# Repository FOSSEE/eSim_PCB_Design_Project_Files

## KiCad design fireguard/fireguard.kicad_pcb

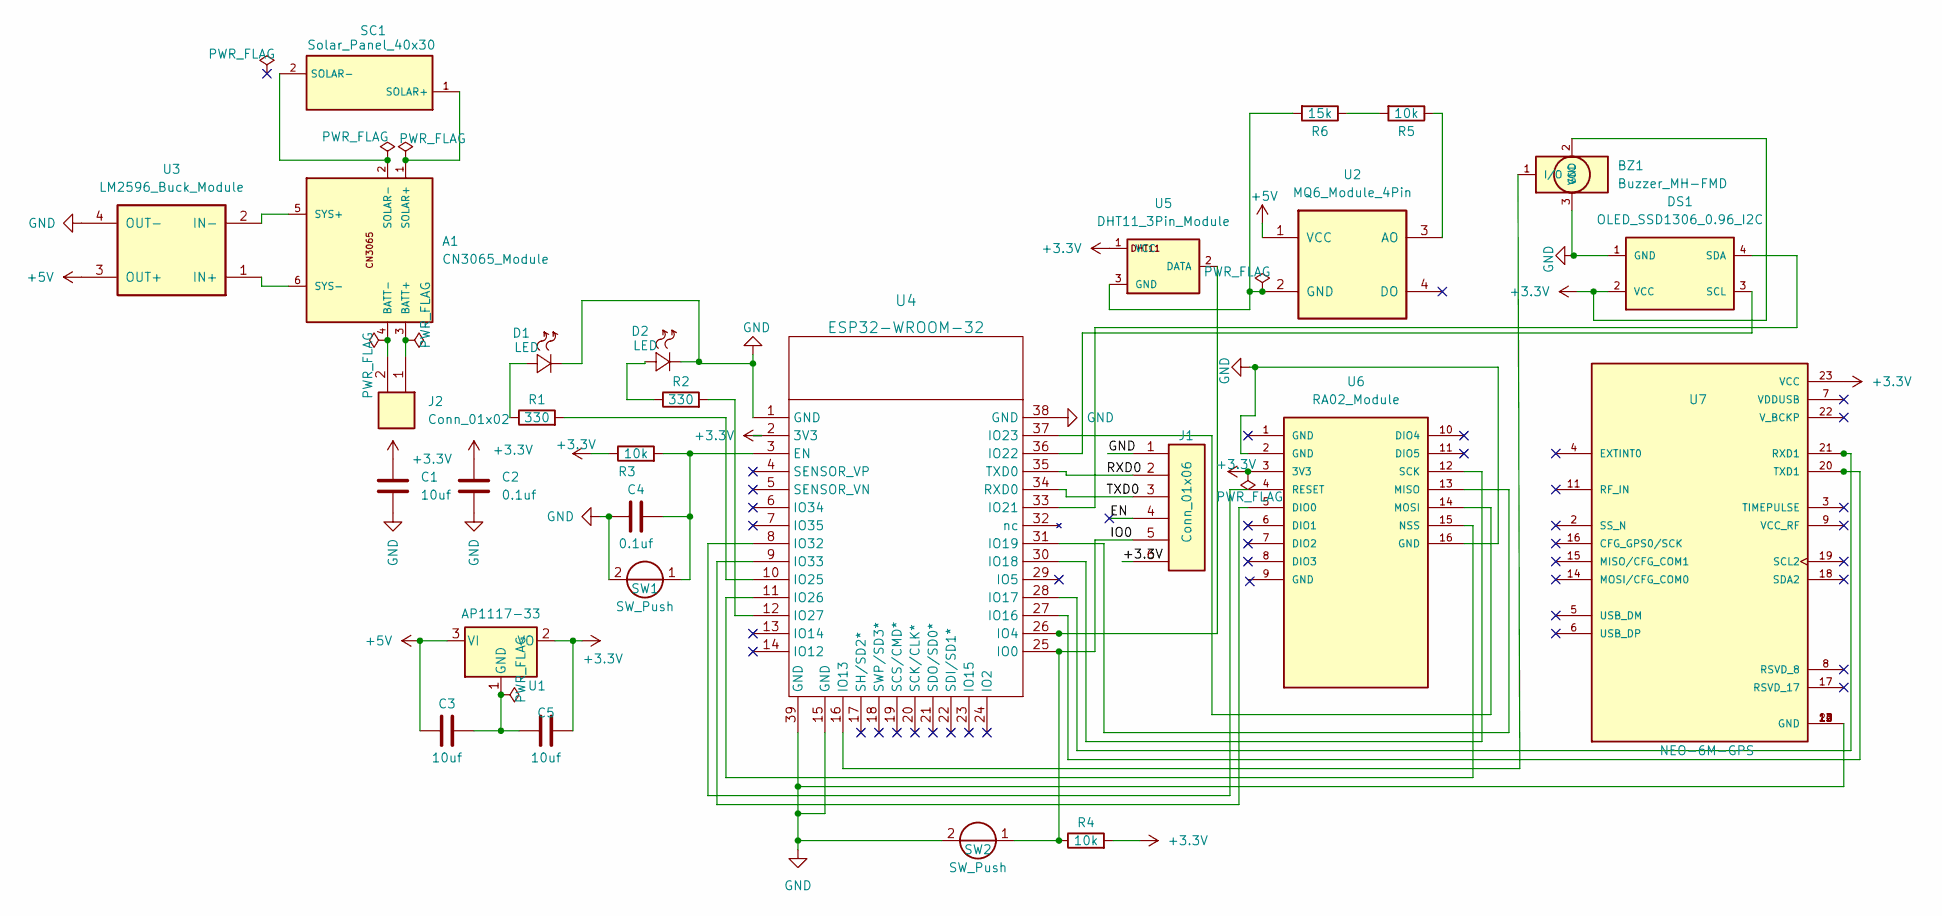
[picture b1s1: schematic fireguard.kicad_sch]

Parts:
A1: CN3065_Module; PinHeader_1x06_P2.54mm_Vertical
BZ1: Buzzer_MH-FMD; PinHeader_1x03_P2.54mm_Vertical_SMD_Pin1Right
C1, C3, C5: 10uf; CP_Radial_D5.0mm_P2.00mm
C2, C4: 0.1uf; C_Disc_D5.0mm_W2.5mm_P5.00mm
D1, D2: LED; LED_D5.0mm
DS1: OLED_SSD1306_0.96_I2C; PinHeader_1x04_P2.54mm_Vertical
J1: Conn_01x06; PinHeader_1x06_P2.54mm_Vertical
J2: Conn_01x02; PinHeader_1x02_P2.54mm_Vertical
R1, R2: 330; R_Axial_DIN0207_L6.3mm_D2.5mm_P10.16mm_Horizontal
R3, R4, R5: 10k; R_Axial_DIN0207_L6.3mm_D2.5mm_P10.16mm_Horizontal
R6: 15k; R_Axial_DIN0207_L6.3mm_D2.5mm_P10.16mm_Horizontal
SC1: Solar_Panel_40x30; PinHeader_1x02_P2.54mm_Vertical
SW1, SW2: SW_Push; SW_PUSH_6mm
U1: AP1117-33; SOT-223-3_TabPin2
U2: MQ6_Module_4Pin; PinHeader_1x04_P2.54mm_Vertical
U3: LM2596_Buck_Module; PinHeader_1x04_P2.54mm_Vertical
U4: ESP32-WROOM-32
U5: DHT11_3Pin_Module; PinHeader_1x03_P2.54mm_Vertical_SMD_Pin1Left
U6: RA02_Module; PinHeader_1x16_P2.54mm_Vertical_SMD_Pin1Right
U7: NEO-6M-GPS; ublox_NEO; PARTREV R15

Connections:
+3.3V: BZ1.2 (VCC), C1.1, C2.1, C5.2, DS1.2 (VCC), J1.6, R3.1, R4.2, U1.2 (VO), U4.2 (3V3), U5.1 (VCC), U6.3 (3V3), U7.23 (VCC)
+5V: C3.1, U1.3 (VI), U2.1 (VCC), U3.3 (OUT+)
/EN: J1.4
/IO0: J1.5, R4.1, SW2.1, U4.25 (IO0)
/RXD0: J1.2, U4.35 (TXD0)
/TXD0: J1.3, U4.34 (RXD0)
GND: BZ1.3 (GND), C1.2, C2.2, C4.2, D1.2 (-), D2.2 (-), DS1.1 (GND), J1.1, SW1.2, SW2.2, U3.4 (OUT-), U4.1 (GND), U4.15 (GND), U4.38 (GND), U4.39 (GND), U6.2 (GND), U6.16 (GND), U7.10 (GND), U7.12 (GND), U7.13 (GND), U7.24 (GND)
unnamed: A1.1 (SOLAR+), SC1.1 (SOLAR+)
unnamed: A1.2 (SOLAR-), SC1.2 (SOLAR-)
unnamed: A1.3 (BATT+), J2.1
unnamed: A1.4 (BATT-), J2.2
unnamed: A1.5 (SYS+), U3.2 (IN-)
unnamed: A1.6 (SYS-), U3.1 (IN+)
unnamed: BZ1.1 (I/O), U4.16 (IO13)
unnamed: C3.2, C5.1, U1.1 (GND)
unnamed: C4.1, R3.2, SW1.1, U4.3 (EN)
unnamed: DS1.3 (SCL), U4.36 (IO22)
unnamed: DS1.4 (SDA), U4.33 (IO21)
unnamed: D1.1 (+), R1.1
unnamed: R1.2, U4.10 (IO25)
unnamed: D2.1 (+), R2.1
unnamed: R2.2, U4.12 (IO27)
unnamed: R5.1, U2.3 (AO)
unnamed: R5.2, R6.1
unnamed: R6.2, U2.2 (GND), U5.3 (GND)
unnamed: U4.8 (IO32), U6.4 (RESET)
unnamed: U4.9 (IO33), U6.5 (DIO0)
unnamed: U4.11 (IO26), U6.15 (NSS)
unnamed: U4.26 (IO4), U5.2 (DATA)
unnamed: U4.27 (IO16), U7.20 (TXD1)
unnamed: U4.28 (IO17), U7.21 (RXD1)
unnamed: U4.30 (IO18), U6.12 (SCK)
unnamed: U4.31 (IO19), U6.13 (MISO)
unnamed: U4.37 (IO23), U6.14 (MOSI)

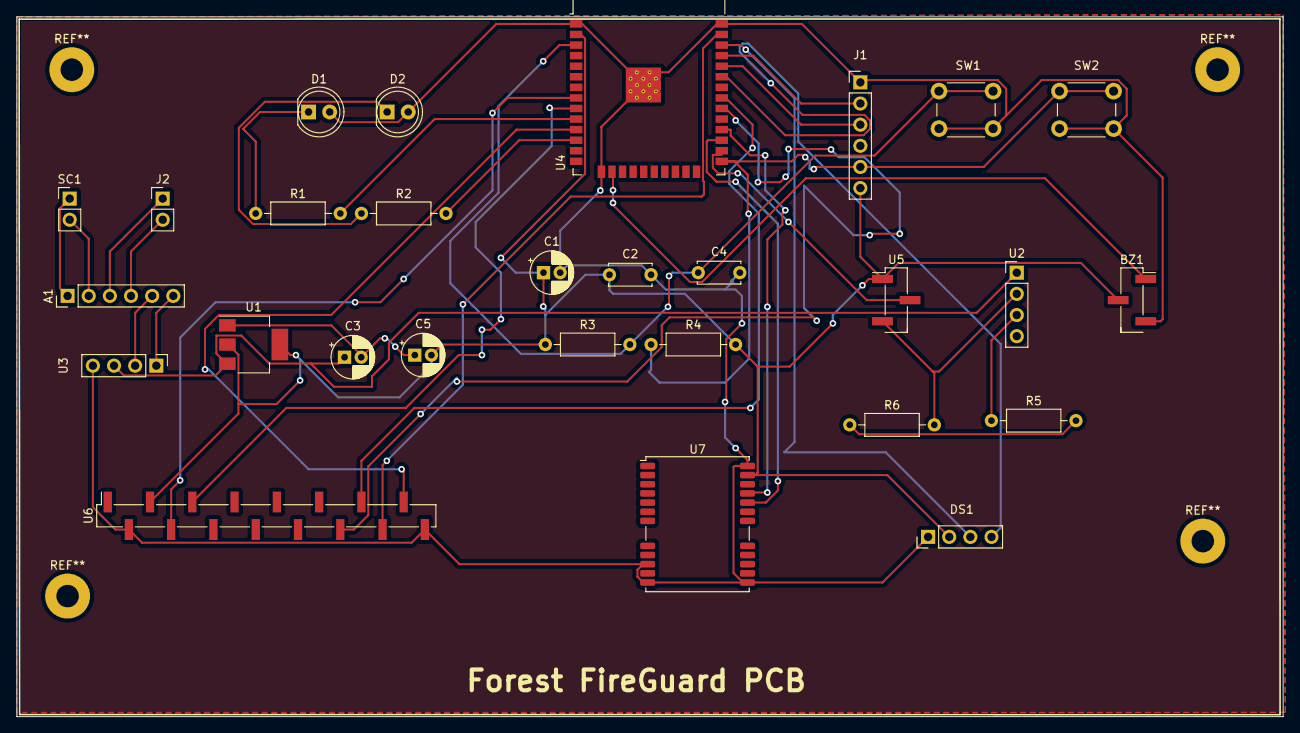
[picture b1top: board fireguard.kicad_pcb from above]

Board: 2 copper layers, 152.1 x 84.1 mm, 28 parts (0 on the bottom side), 33 nets.

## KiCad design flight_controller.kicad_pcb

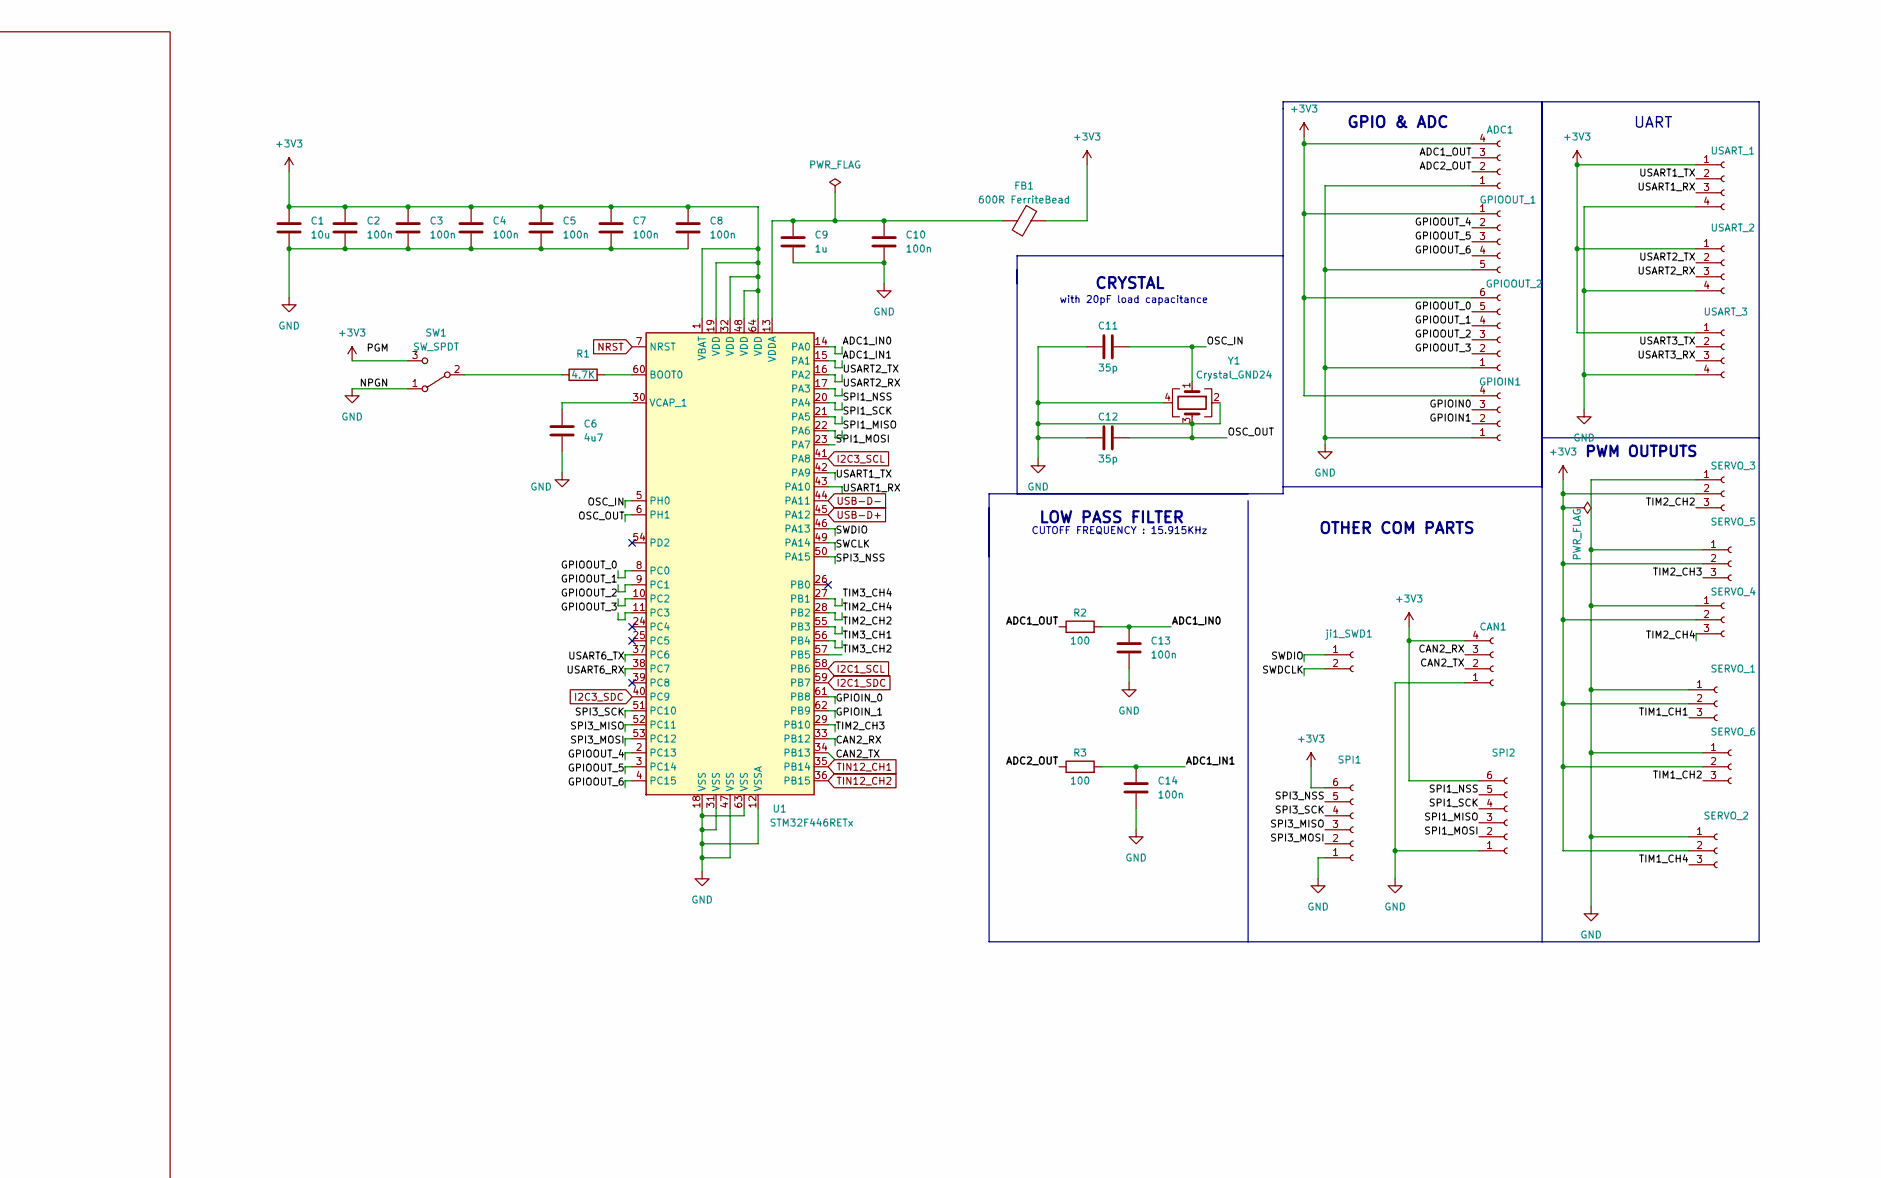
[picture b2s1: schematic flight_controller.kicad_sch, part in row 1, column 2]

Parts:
ADC1: PinHeader_1x04_P1.00mm_Vertical
C1: 10u; C_0603_1608Metric
C2, C3, C4, C5, C7, C8, C10, C13, C14: 100n; C_0603_1608Metric
C6: 4u7; C_0603_1608Metric
C9: 1u; C_0603_1608Metric
C11, C12: 35p; C_0603_1608Metric
CAN1: PinHeader_1x04_P1.00mm_Vertical
FB1: 600R FerriteBead; LairdTech_28C0236-0JW-10
GPIOIN1: PinHeader_1x04_P1.00mm_Vertical
GPIOOUT_1: PinHeader_1x05_P1.00mm_Vertical
GPIOOUT_2: PinHeader_1x06_P1.00mm_Vertical
R1: 4.7K; R_0603_1608Metric
R2, R3: 100; R_0603_1608Metric
SERVO_1, SERVO_2, SERVO_3, SERVO_4, SERVO_5, SERVO_6: PinHeader_1x03_P1.00mm_Vertical
SPI1, SPI2: PinHeader_1x06_P1.00mm_Vertical
SW1: SW_SPDT; SW_SPDT_CK-JS102011SAQN
U1: STM32F446RETx; LQFP-64_10x10mm_P0.5mm
USART_1, USART_2, USART_3: PinHeader_1x04_P1.00mm_Vertical
Y1: Crystal_GND24; Crystal_SMD_0603-4Pin_6.0x3.5mm
ji1_SWD1: PinHeader_1x02_P1.00mm_Vertical

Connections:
+3V3: ADC1.4, C1.1, C2.1, C3.1, C4.1, C5.1, C7.1, C8.1, CAN1.4, FB1.1, GPIOIN1.4, GPIOOUT_1.1, GPIOOUT_2.6, SERVO_1.2, SERVO_2.2, SERVO_3.2, SERVO_4.2, SERVO_5.2, SERVO_6.2, SPI1.6, SPI2.6, SW1.3 (C), U1.1 (VBAT), U1.19 (VDD), U1.32 (VDD), U1.48 (VDD), U1.64 (VDD), USART_1.1, USART_2.1, USART_3.1; also elsewhere on the board
/ADC1_IN0: C13.1, R2.2, U1.14 (PA0)
/ADC1_IN1: C14.1, R3.2, U1.15 (PA1)
/ADC1_OUT: ADC1.3, R2.1
/ADC2_OUT: ADC1.2, R3.1
/CAN2_RX: CAN1.3, U1.33 (PB12)
/CAN2_TX: CAN1.2, U1.34 (PB13)
/GPIOIN0: GPIOIN1.3
/GPIOIN1: GPIOIN1.2
/GPIOIN_0: U1.61 (PB8)
/GPIOIN_1: U1.62 (PB9)
/GPIOOUT_0: GPIOOUT_2.5, U1.8 (PC0)
/GPIOOUT_1: GPIOOUT_2.4, U1.9 (PC1)
/GPIOOUT_2: GPIOOUT_2.3, U1.10 (PC2)
/GPIOOUT_3: GPIOOUT_2.2, U1.11 (PC3)
/GPIOOUT_4: GPIOOUT_1.2, U1.2 (PC13)
/GPIOOUT_5: GPIOOUT_1.3, U1.3 (PC14)
/GPIOOUT_6: GPIOOUT_1.4, U1.4 (PC15)
/OSC_IN: C11.2, U1.5 (PH0), Y1.1
/SPI1_MISO: SPI2.3, U1.22 (PA6)
/SPI1_MOSI: SPI2.2, U1.23 (PA7)
/SPI1_NSS: SPI2.5, U1.20 (PA4)
/SPI1_SCK: SPI2.4, U1.21 (PA5)
/SPI3_MISO: SPI1.3, U1.52 (PC11)
/SPI3_MOSI: SPI1.2, U1.53 (PC12)
/SPI3_NSS: SPI1.5, U1.50 (PA15)
/SPI3_SCK: SPI1.4, U1.51 (PC10)
/SWCLK: U1.49 (PA14)
/SWDCLK: ji1_SWD1.2
/SWDIO: U1.46 (PA13), ji1_SWD1.1
/TIM1_CH1: SERVO_1.3
/TIM1_CH2: SERVO_6.3
/TIM1_CH4: SERVO_2.3
/TIM2_CH2: SERVO_3.3, U1.55 (PB3)
/TIM2_CH3: SERVO_5.3, U1.29 (PB10)
/TIM2_CH4: SERVO_4.3, U1.28 (PB2)
/TIM3_CH1: U1.56 (PB4)
/TIM3_CH2: U1.57 (PB5)
/TIM3_CH4: U1.27 (PB1)
/USART1_RX: U1.43 (PA10), USART_1.3
/USART1_TX: U1.42 (PA9), USART_1.2
/USART2_RX: U1.17 (PA3), USART_2.3
/USART2_TX: U1.16 (PA2), USART_2.2
/USART3_RX: USART_3.3
/USART3_TX: USART_3.2
/USART6_RX: U1.38 (PC7)
/USART6_TX: U1.37 (PC6)
GND: ADC1.1, C1.2, C2.2, C3.2, C4.2, C5.2, C6.2, C7.2, C8.2, C9.2, C10.2, C11.1, C12.1, C12.2, C13.2, C14.2, CAN1.1, GPIOIN1.1, GPIOOUT_1.5, GPIOOUT_2.1, SERVO_1.1, SERVO_2.1, SERVO_3.1, SERVO_4.1, SERVO_5.1, SERVO_6.1, SPI1.1, SPI2.1, SW1.1 (A), U1.6 (PH1), U1.12 (VSSA), U1.18 (VSS), U1.31 (VSS), U1.47 (VSS), U1.63 (VSS), USART_1.4, USART_2.4, USART_3.4, Y1.2, Y1.3, Y1.4; also elsewhere on the board
I2C1_SCL: U1.58 (PB6); also elsewhere on the board
I2C1_SDC: U1.59 (PB7)
I2C3_SCL: U1.41 (PA8); also elsewhere on the board
I2C3_SDC: U1.40 (PC9)
NRST: U1.7 (NRST); also elsewhere on the board
unnamed: C6.1, U1.30 (VCAP_1)
unnamed: C9.1, C10.1, FB1.2, U1.13 (VDDA)
unnamed: R1.1, SW1.2 (B)
unnamed: R1.2, U1.60 (BOOT0)
TIN12_CH1: U1.35 (PB14)
TIN12_CH2: U1.36 (PB15)
USB-D+: U1.45 (PA12)
USB-D-: U1.44 (PA11); also elsewhere on the board

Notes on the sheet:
CUTOFF FREQUENCY : 15.915KHz
UART
GPIO & ADC
CRYSTAL
PWM OUTPUTS
with 20pF load capacitance
LOW PASS FILTER
OTHER COM PARTS

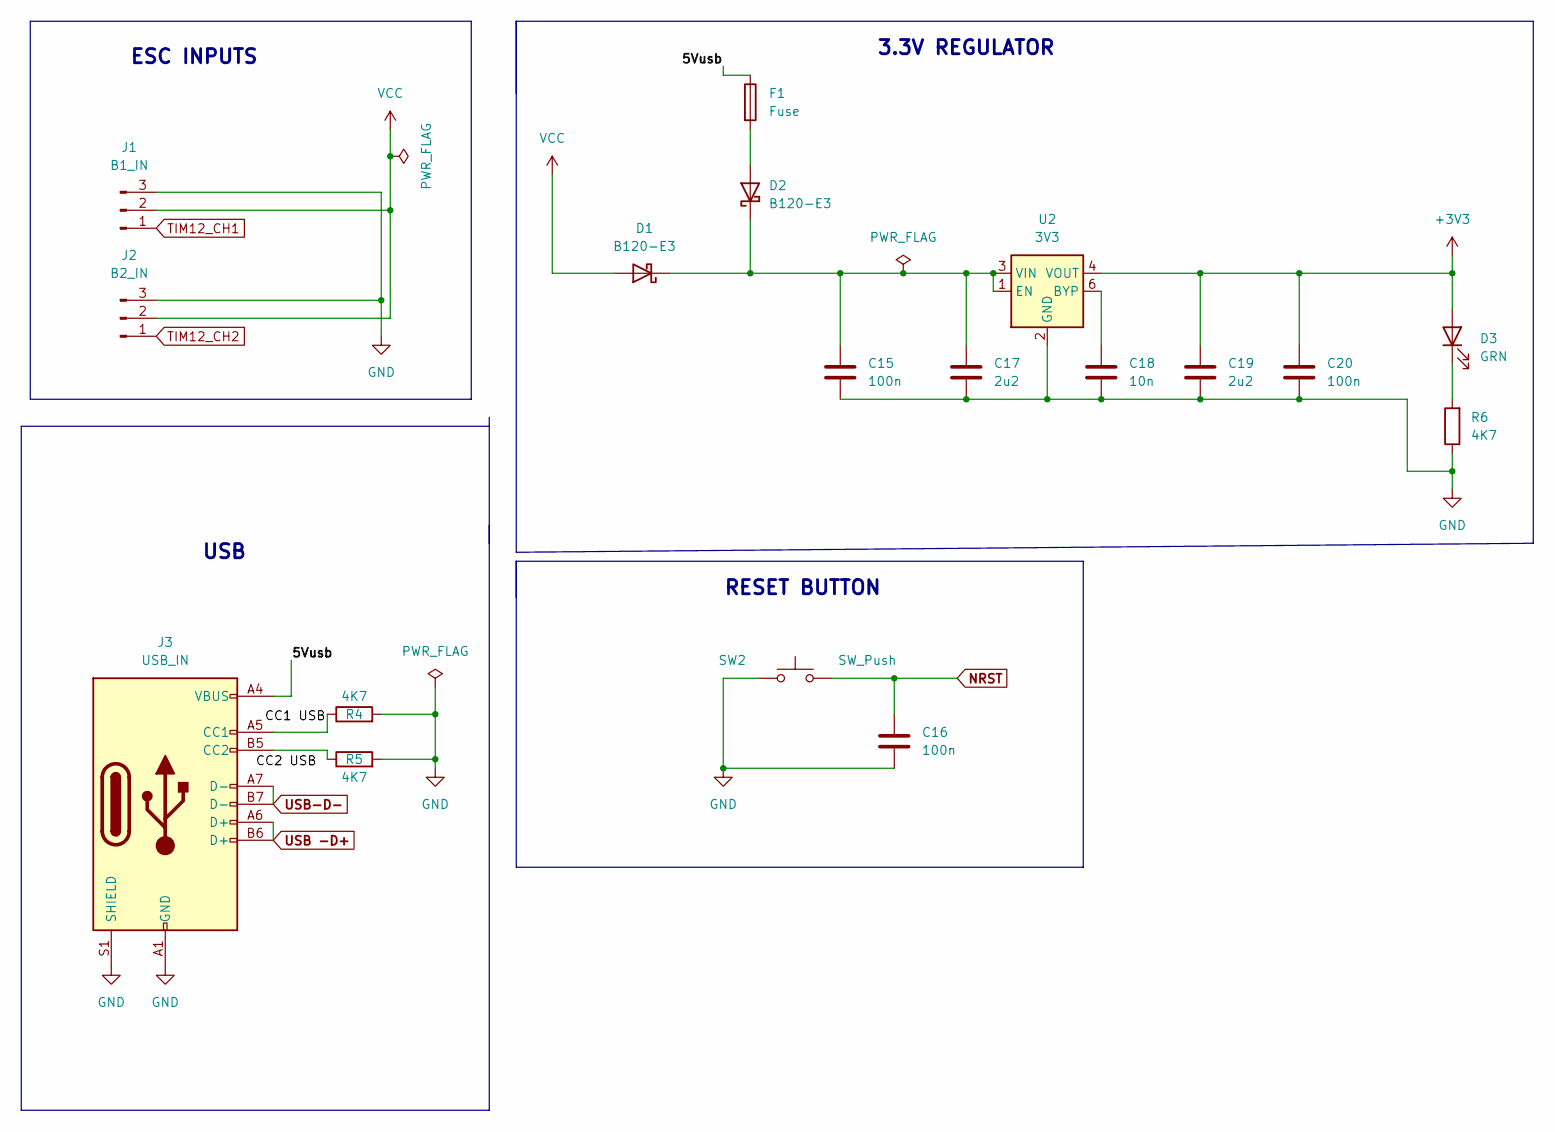
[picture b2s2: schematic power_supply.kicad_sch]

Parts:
C15, C16, C20: 100n; C_0603_1608Metric
C17, C19: 2u2; C_0603_1608Metric
C18: 10n; C_0603_1608Metric
D1, D2: B120-E3; D_SMA
D3: GRN; LED_0603_1608Metric
F1: Fuse; Fuse_0603_1608Metric
J1: B1_IN; FanPinHeader_1x03_P2.54mm_Vertical
J2: B2_IN; FanPinHeader_1x03_P2.54mm_Vertical
J3: USB_IN; USB_C_Receptacle_Amphenol_12401610E4-2A
R4, R5, R6: 4K7; R_0603_1608Metric
SW2: SW_Push; SW_PUSH-12mm
U2: 3V3; MLF-6-1EP_1.6x1.6mm_P0.5mm_EP0.5x1.26mm

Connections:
+3V3: C19.1, C20.1, D3.2 (A), U2.4 (VOUT); also elsewhere on the board
/POWER/5Vusb: F1.1, J3.A4 (VBUS), J3.A9 (VBUS), J3.B4 (VBUS), J3.B9 (VBUS)
GND: C15.2, C16.2, C17.2, C18.2, C19.2, C20.2, J1.3, J2.3, J3.A1 (GND), J3.A12 (GND), J3.B1 (GND), J3.B12 (GND), J3.S1 (SHIELD), R4.2, R5.2, R6.1, SW2.1, U2.2 (GND), U2.7 (GND); also elsewhere on the board
NRST: C16.1, SW2.2; also elsewhere on the board
unnamed: C15.1, C17.1, D1.1 (K), D2.1 (K), U2.1 (EN), U2.3 (VIN)
unnamed: C18.1, U2.6 (BYP)
unnamed: D2.2 (A), F1.2
unnamed: D3.1 (K), R6.2
unnamed: J3.A5 (CC1), R4.1
unnamed: J3.B5 (CC2), R5.1
TIM12_CH1: J1.1
TIM12_CH2: J2.1
USB -D+: J3.A6 (D+), J3.B6 (D+)
USB-D-: J3.A7 (D-), J3.B7 (D-); also elsewhere on the board
VCC: D1.2 (A), J1.2, J2.2

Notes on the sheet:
RESET BUTTON
USB
3.3V REGULATOR
ESC INPUTS

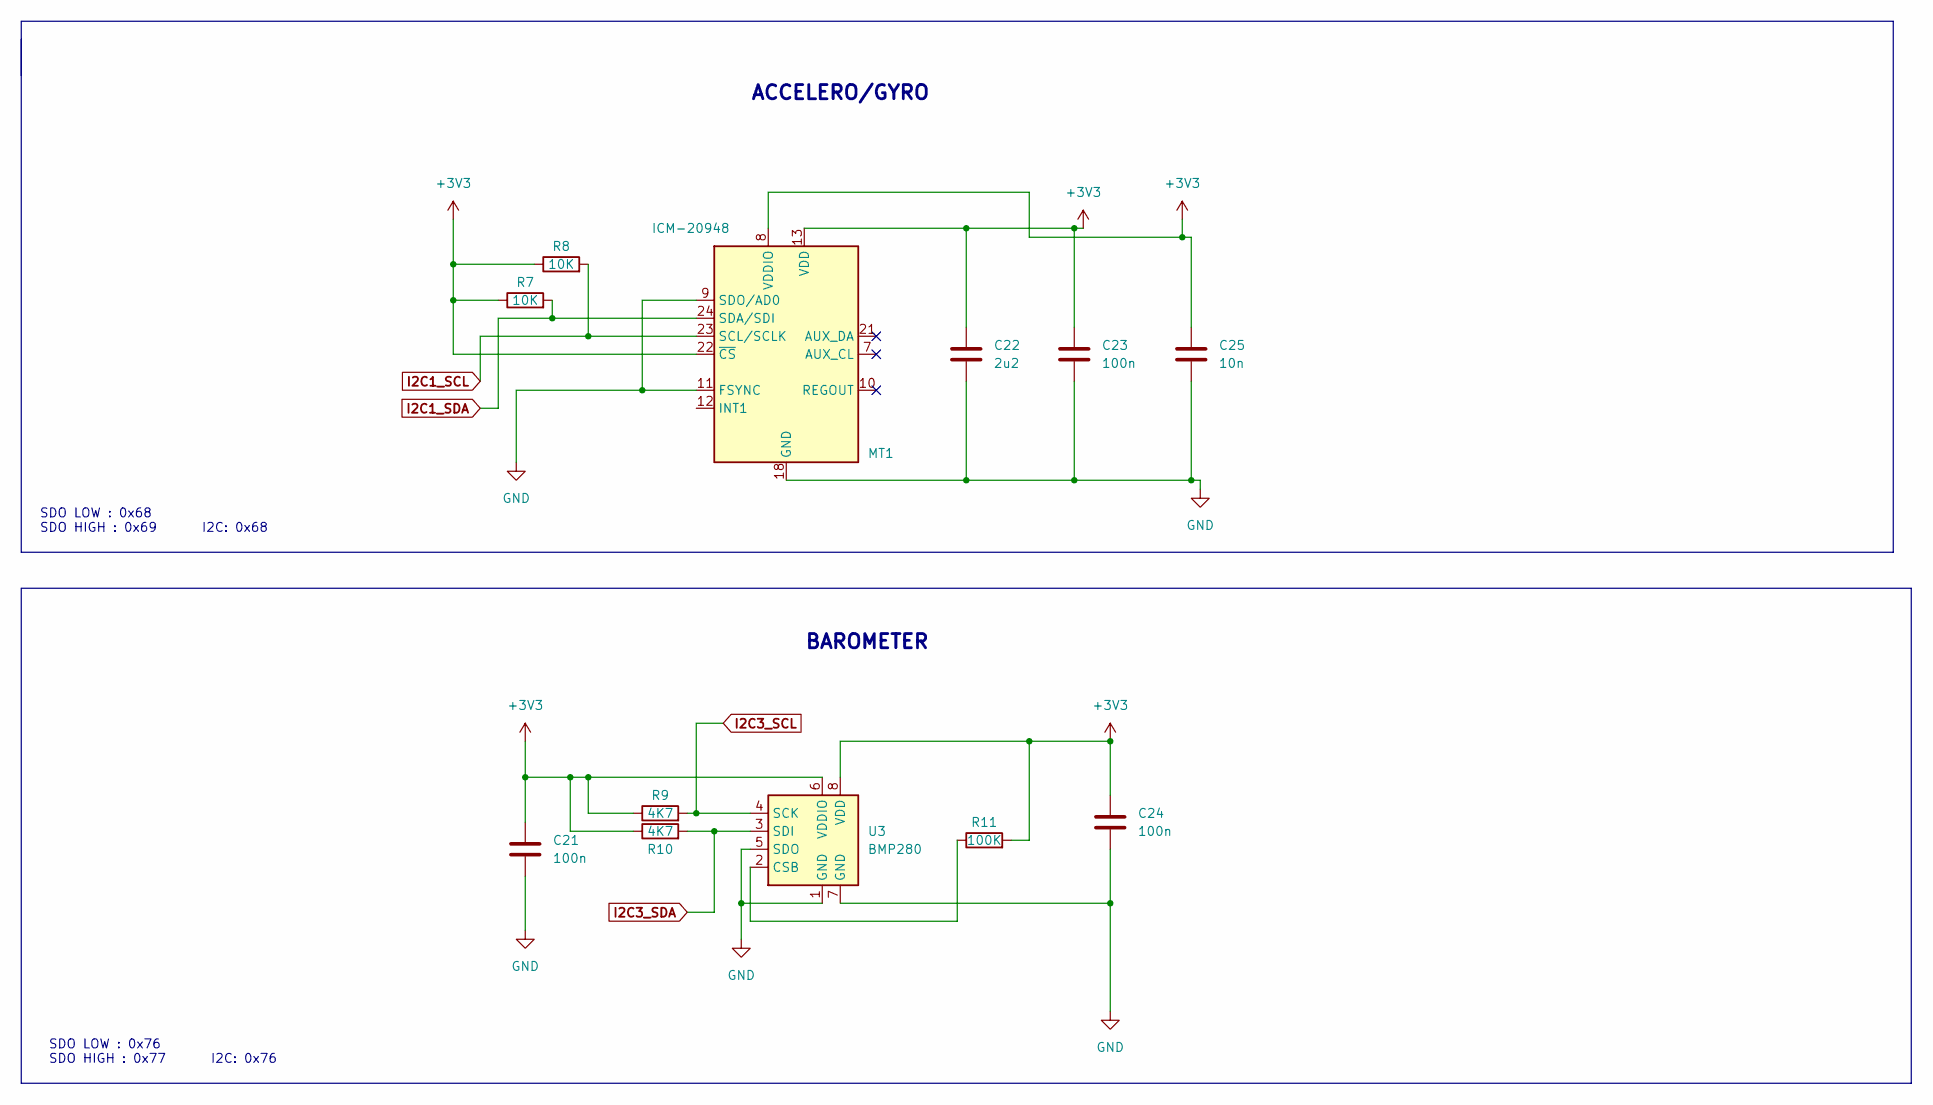
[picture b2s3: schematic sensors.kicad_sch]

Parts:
C21, C23, C24: 100n; C_0603_1608Metric
C22: 2u2; C_0603_1608Metric
C25: 10n; C_0603_1608Metric
MT1: ICM-20948; InvenSense_QFN-24_3x3mm_P0.4mm
R7, R8: 10K; R_0603_1608Metric
R9, R10: 4K7; R_0603_1608Metric
R11: 100K; R_0603_1608Metric
U3: BMP280; Bosch_LGA-8_2x2.5mm_P0.65mm_ClockwisePinNumbering

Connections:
+3V3: C21.1, C22.1, C23.1, C24.1, C25.1, MT1.8 (VDDIO), MT1.13 (VDD), MT1.22 (~CS), R7.1, R8.1, R9.1, R10.1, R11.2, U3.6 (VDDIO), U3.8 (VDD); also elsewhere on the board
GND: C21.2, C22.2, C23.2, C24.2, C25.2, MT1.9 (SDO/AD0), MT1.11 (FSYNC), MT1.18 (GND), MT1.20 (GND), U3.1 (GND), U3.5 (SDO), U3.7 (GND); also elsewhere on the board
I2C1_SCL: MT1.23 (SCL/SCLK), R8.2; also elsewhere on the board
I2C1_SDA: MT1.24 (SDA/SDI), R7.2
I2C3_SCL: R9.2, U3.4 (SCK); also elsewhere on the board
I2C3_SDA: R10.2, U3.3 (SDI)
unnamed: R11.1, U3.2 (CSB)

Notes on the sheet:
BAROMETER
ACCELERO/GYRO
I2C: 0x68
SDO LOW : 0x76 SDO HIGH : 0x77
SDO LOW : 0x68 SDO HIGH : 0x69
I2C: 0x76

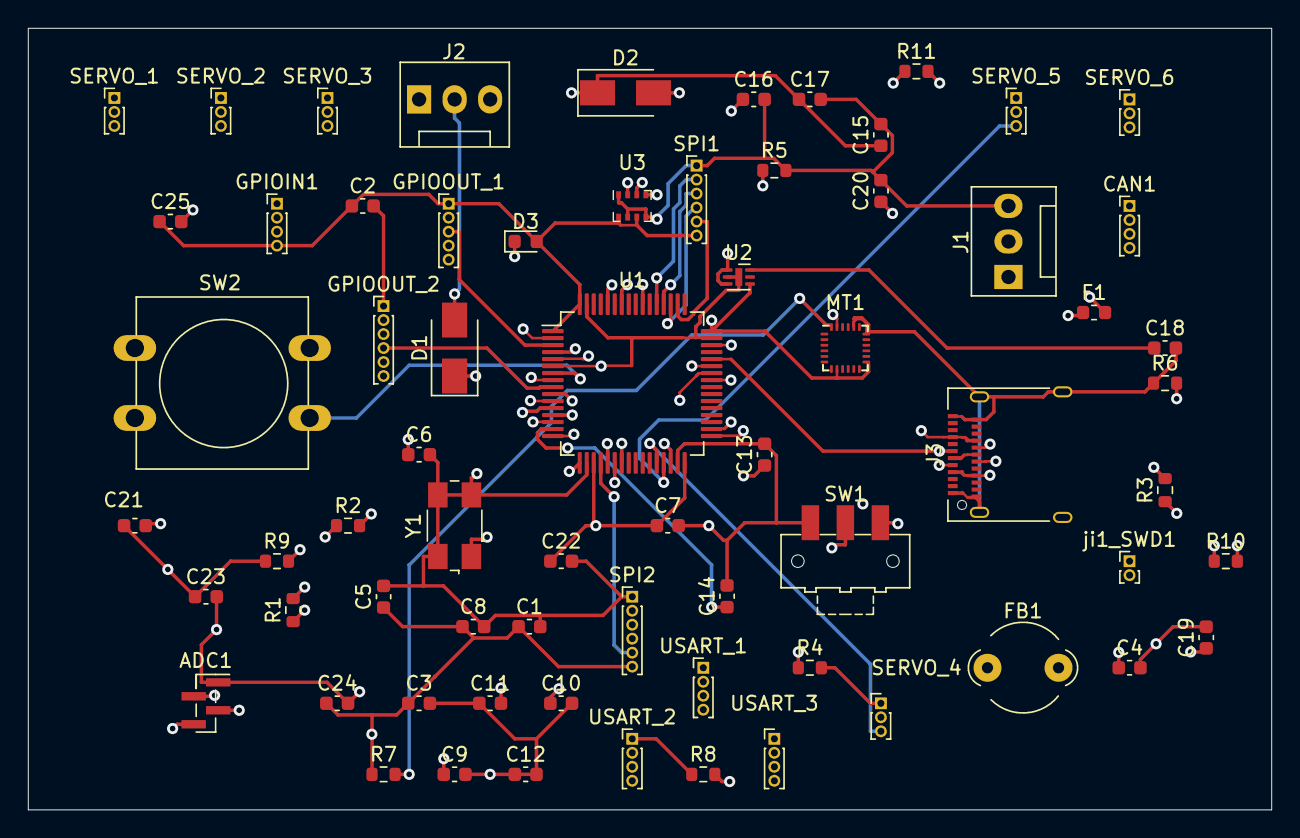
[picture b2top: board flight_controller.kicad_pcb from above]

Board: 4 copper layers, 88.9 x 55.9 mm, 68 parts (0 on the bottom side), 52 nets.

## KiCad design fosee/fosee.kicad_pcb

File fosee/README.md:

# ATmega328P Environment Monitor (eSim 2.5 PCB Project)

A 2-layer PCB design for a small environment-monitoring board built around an **ATmega328P (ATMEGA328P-AU, TQFP-32)**. The board reads temperature/humidity (DHT11) and ambient light (LDR), shows data on an I2C OLED, gives feedback through three status LEDs and a buzzer, and can be programmed over ICSP or a UART header.

- **Author:** Mohnish Sathiamurthy, Dept. of ECE, Chennai Institute of Technology
- **Tool:** eSim 2.5 (Eeschema / Pcbnew, KiCad 6.0 file format)
- **Board:** 2 layers, [100 x 80] mm, GND copper pour on the bottom layer
- **Status:** schematic complete, layout complete, DRC: [fill in result, e.g. 0 errors / 0 unconnected]

> Items in `[square brackets]` are values to confirm or fill in from your final design before submission.

---

## 1. Features

| Function | Implementation |
|---|---|
| Processing | ATmega328P-AU, 16 MHz crystal, 5 V |
| Power input | DC barrel jack, reverse-polarity diode, L7805 (5 V), AMS1117-3.3 (3.3 V) |
| Programming | 6-pin ICSP header, 4-pin UART header |
| Sensing | DHT11 (temperature/humidity) header, LDR light divider on ADC0 |
| Display | 4-pin I2C OLED header (3.3 V, with 4.7 kOhm pull-ups) |
| Indicators | 3 status LEDs (330 Ohm), buzzer driven by BC547 with flyback diode |
| Mechanical | 4 x M3 mounting holes, connectors placed on the board edges |

## 2. Circuit description

**Power.** The jack (J1) feeds D1 (1N4007, reverse-polarity protection) to the `VIN` rail. U1 (L7805) generates the 5 V `VCC` rail (C1 0.33 uF in, C2 0.1 uF out). U2 (AMS1117-3.3) takes `VCC` and generates `+3V3` for the OLED (C3 10 uF in, C4 22 uF out).

**Microcontroller.** U3 is powered from `VCC` on VCC and AVCC pins, each decoupled with 100 nF (C5, C6, C7). AREF is decoupled with C8 (100 nF). All GND pins connect to the ground plane.

**Clock and reset.** Y1 (16 MHz) with C9/C10 (22 pF) sits on XTAL1/XTAL2. RESET is pulled up by R1 (10 kOhm) with SW1 to ground, and is also brought to the ICSP header.

**Sensors.** The DHT11 data line (PD2) has a 10 kOhm pull-up (R2). The LDR (J6) forms a divider with R3 (10 kOhm); the midpoint `LDR_OUT` goes to PC0 (ADC0).

**Display.** The OLED header (J5) uses PC4 (SDA) and PC5 (SCL) with 4.7 kOhm pull-ups (R4, R5) to 3.3 V.

**Outputs.** PD4/PD5/PD6 drive LEDs D2-D4 through 330 Ohm resistors (R6-R8). PD7 drives Q1 (BC547) through R9 (1 kOhm); BZ1 sits between `VCC` and the collector with D5 (1N4148) as a flyback diode.

## 3. MCU pin assignment

| Pin | Name | Net | Use |
|---|---|---|---|
| 2 | PD4 | LED1 | Status LED 1 |
| 9 | PD5 | LED2 | Status LED 2 |
| 10 | PD6 | LED3 | Status LED 3 |
| 11 | PD7 | BUZ | Buzzer driver |
| 15 | PB3 | MOSI | ICSP |
| 16 | PB4 | MISO | ICSP |
| 17 | PB5 | SCK | ICSP |
| 7 / 8 | PB6 / PB7 | XTAL1 / XTAL2 | 16 MHz crystal |
| 23 | PC0 | LDR_OUT | Light sensor (ADC0) |
| 27 | PC4 | SDA | OLED (I2C) |
| 28 | PC5 | SCL | OLED (I2C) |
| 29 | PC6 | RESET | Reset / ICSP |
| 30 | PD0 | UART_RX | UART header |
| 31 | PD1 | UART_TX | UART header |
| 32 | PD2 | DHT_DATA | DHT11 data |
| 4, 6, 18 | VCC, VCC, AVCC | VCC | 5 V supply |
| 3, 5, 21 | GND | GND | Ground |
| 20 | AREF | AREF | Decoupled with C8 |
| 1, 12, 13, 14, 19, 22, 24, 25, 26 | - | - | Unused (no-connect) |

## 4. Connectors (board edge)

| Ref | Function | Pins |
|---|---|---|
| J1 | DC power jack | 1 = tip (+), 2 = sleeve (GND), MP = shield |
| J2 | ICSP (2x3) | 1 MISO, 2 VCC, 3 SCK, 4 MOSI, 5 RESET, 6 GND |
| J3 | UART (1x4) | 1 GND, 2 VCC, 3 UART_TX, 4 UART_RX |
| J4 | DHT11 (1x3) | 1 VCC, 2 DATA, 3 GND |
| J5 | OLED I2C (1x4) | 1 GND, 2 +3V3, 3 SCL, 4 SDA |
| J6 | LDR (1x2) | 1 VCC, 2 LDR_OUT |

Connect the UART header to a USB-serial adapter as: adapter RX to J3 pin 3, adapter TX to J3 pin 4, GND to GND. Use 5 V logic levels.

## 5. Bill of materials

| Ref | Value | Footprint |
|---|---|---|
| U3 | ATMEGA328P-AU | TQFP-32_7x7mm_P0.8mm |
| U1 | L7805 | TO-220-3_Vertical |
| U2 | AMS1117-3.3 | SOT-223-3_TabPin2 |
| Q1 | BC547 | TO-92_Inline |
| D1 | 1N4007 | D_DO-41_SOD81_P10.16mm_Horizontal |
| D5 | 1N4148 | D_DO-35_SOD27_P7.62mm_Horizontal |
| D2-D4 | LED | LED_0805_2012Metric |
| Y1 | 16 MHz | Crystal_HC49-4H_Vertical |
| SW1 | Reset switch | SW_PUSH_6mm |
| BZ1 | Buzzer | Buzzer_12x9.5RM7.6 |
| R1-R3 | 10 kOhm | R_0805_2012Metric |
| R4, R5 | 4.7 kOhm | R_0805_2012Metric |
| R6-R8 | 330 Ohm | R_0805_2012Metric |
| R9 | 1 kOhm | R_0805_2012Metric |
| C1 | 0.33 uF | C_0805_2012Metric |
| C2 | 0.1 uF | C_0805_2012Metric |
| C3 | 10 uF | C_0805_2012Metric |
| C4 | 22 uF | C_0805_2012Metric |
| C5-C8 | 100 nF | C_0805_2012Metric |
| C9, C10 | 22 pF | C_0805_2012Metric |
| J1 | DC jack | BarrelJack_CUI_PJ-063AH_Horizontal |
| J2 | ICSP | PinHeader_2x03_P2.54mm_Vertical |
| J3, J5 | 1x4 header | PinHeader_1x04_P2.54mm_Vertical |
| J4 | 1x3 header | PinHeader_1x03_P2.54mm_Vertical |
| J6 | 1x2 header | PinHeader_1x02_P2.54mm_Vertical |
| H1-H4 | M3 hole | MountingHole_3.2mm_M3 |

[Update this table if you changed any value or footprint during layout.]

## 6. PCB design notes

- **Stack-up:** 2 layers (F.Cu, B.Cu). Bottom layer is a filled GND zone; refill with `B` after any change.
- **Track widths:** [signal 0.25 mm / power 0.5-1.0 mm. Replace with the values you used.]
- **Placement:** the crystal and its load capacitors are next to pins 7 and 8; decoupling capacitors sit next to the VCC, AVCC and AREF pins; the regulators are near the DC jack.
- **Edge connectors:** J1 to J6 and the mounting holes are at the board edges. J1's plug opening faces outward.
- **Routing:** power first with wider tracks, then signals, avoiding 90 degree corners; crystal traces kept short.
- **Silkscreen:** reference designators, connector pin 1 markers and a board title.

## 7. Verification

| Check | Result |
|---|---|
| ERC (schematic) | [fill in, e.g. 0 errors] |
| DRC (layout) | [fill in, e.g. 0 errors, 0 unconnected items] |
| All symbols have footprints | [yes / no] |
| 3D viewer reviewed (top, bottom, isometric) | [yes / no] |
| Reopened in a fresh eSim 2.5 install | [yes / no] |

## 7a. Known limitations

- The AMS1117-3.3 regulator can be unstable with low-ESR ceramic output capacitors; a tantalum or electrolytic 22 uF is recommended on a built board.
- The 5 V MCU reads the OLED bus through 3.3 V pull-ups; this works with the AVR input thresholds, but keep the AVR internal pull-ups on SDA/SCL disabled.
- The DHT11 is slow and low-accuracy; it is used here as a simple sensor example.
- [Add anything else you noticed: clearances, parts you would change, etc.]

## 8. Project structure

```
environment/
├── environment.kicad_pro      project settings
├── environment.kicad_sch      schematic
├── environment.kicad_pcb      PCB layout
├── environment.kicad_prl      local project state
├── sym-lib-table              project symbol libraries
├── fp-lib-table               project footprint library (esim_fp)
├── README.md                  this file
├── report/                    PDF report and screenshots
└── lib/
    ├── symbols/               project symbol libraries
    ├── footprints.pretty/     footprints used on the board
    └── 3d/                    3D models (.wrl)
```

All libraries are inside the project folder and referenced with relative paths (`${KIPRJMOD}`), so the project opens in eSim 2.3 / 2.5 without importing anything.

## 9. How to open the project

1. Copy the whole `environment` folder to your eSim workspace.
2. Open eSim, then open the project, then open **Eeschema** and **Pcbnew** from the toolbar.
3. If a library is reported missing: **Preferences, Manage Symbol Libraries / Manage Footprint Libraries, Project Specific Libraries**, and confirm the paths start with `${KIPRJMOD}/lib/`.
4. In Eeschema run **Inspect, Electrical Rules Checker**. In Pcbnew run **Inspect, Design Rules Checker**.

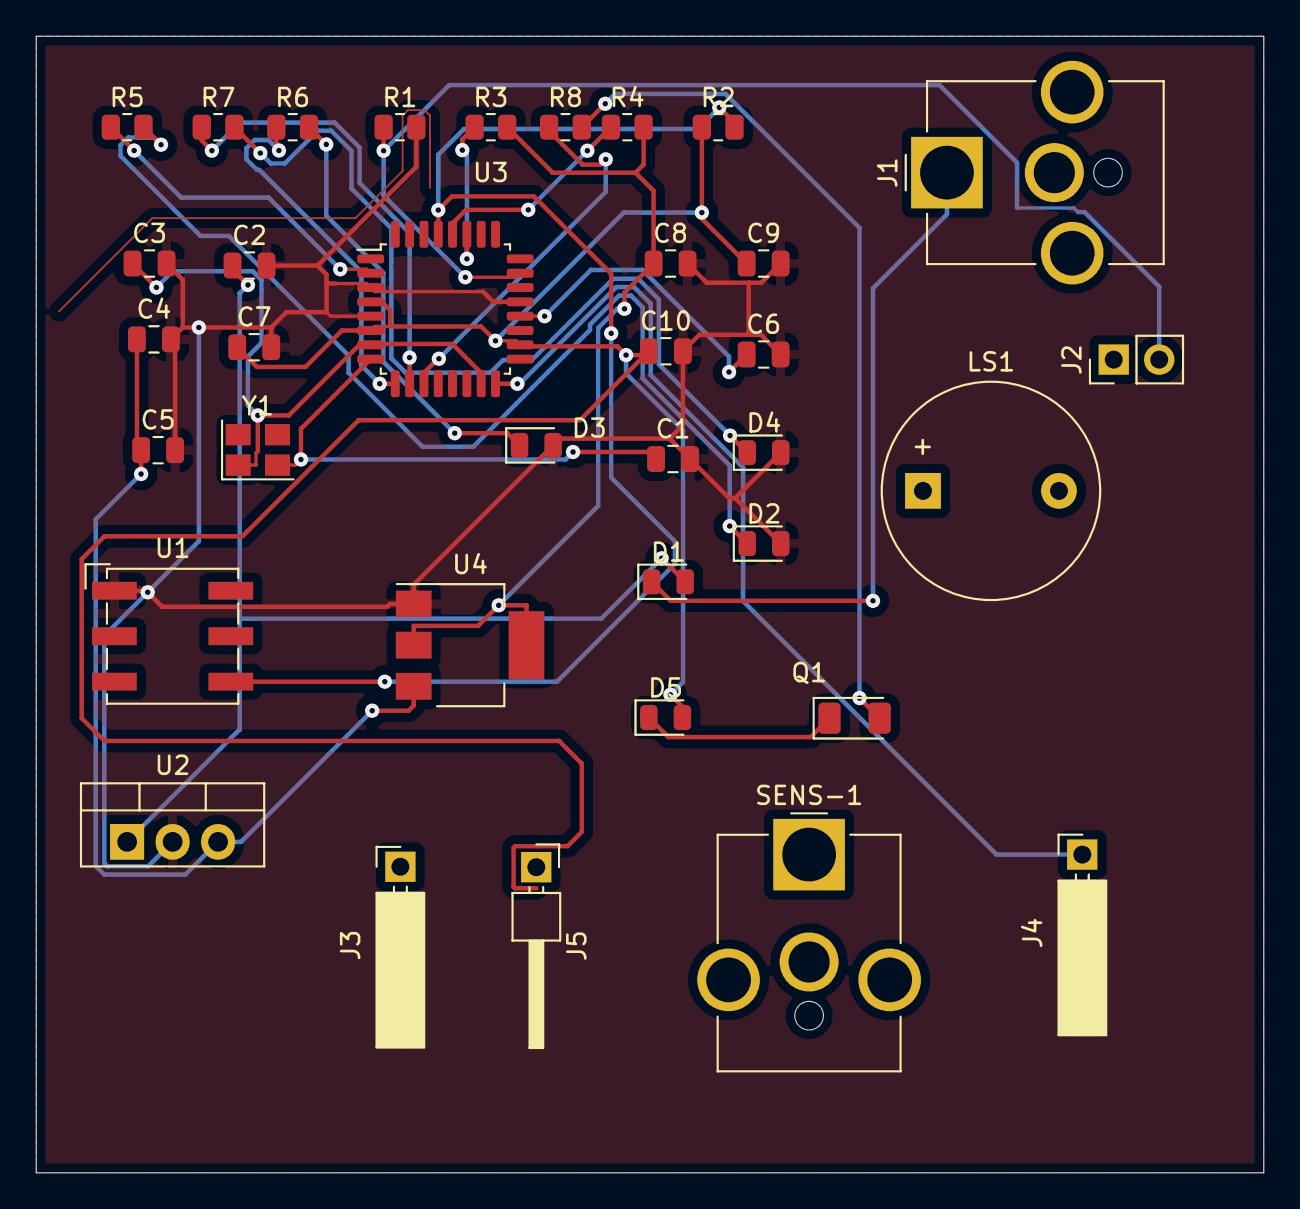
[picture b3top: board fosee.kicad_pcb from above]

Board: 2 copper layers, 68.6 x 63.5 mm, 36 parts (0 on the bottom side), 23 nets.

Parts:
C1, C3, C4, C5: 0.1uF; C_0805_2012Metric
C2: 0.3uF; C_0805_2012Metric
C6, C7, C9, C10: 100nf; C_0805_2012Metric
C8: 22uF; C_0805_2012Metric
D1: D1N4002_PSPICE; D_0805_2012Metric
D2, D3, D4: LED; LED_0805_2012Metric
D5: D1N4148_PSPICE; D_0805_2012Metric
J1: PJ-002A; BarrelJack_CUI_PJ-063AH_Horizontal_CircularHoles
J2: 22284020; PinHeader_1x02_P2.54mm_Vertical
J3: 6130XX11821_61300411821; PinSocket_1x01_P2.54mm_Horizontal
J4: 6130XX21121_61300621121; PinSocket_1x01_P2.54mm_Horizontal
J5: 61300411121; PinHeader_1x01_P2.54mm_Horizontal
LS1: AI-1223-TWT-5V-R; Buzzer_12x9.5RM7.6
Q1: BC547; D_1206_3216Metric
R1, R8: res; R_0805_2012Metric
R2: 10k; R_0805_2012Metric
R3, R4: 4.7K; R_0805_2012Metric
R5, R6, R7: 330; R_0805_2012Metric
SENS-1: DHT11; BarrelJack_CUI_PJ-063AH_Horizontal_CircularHoles
U1: Sw_tClose_PSPICE; Nidec_Copal_SH-7010A
U2: L7805CV; TO-220-3_Vertical
U3: ATMEGA328P-AU; LQFP-32_7x7mm_P0.8mm
U4: AMS1117-5.0; SOT-223-3_TabPin2
Y1: ABLS-16.000MHZ-B2-T; Crystal_SMD_3225-4Pin_3.2x2.5mm

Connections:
+3V3: C8.1, R3.2 (B), R4.2 (B), U4.2 (VOUT)
GND: C1.2, C2.2, C3.2, C4.2, C5.2, C6.2, C7.2, C8.2, C9.2, C10.2, D2.2 (-), D3.2 (-), D4.2 (-), R1.2 (B), U1.1, U2.2 (GROUND), U3.3 (GND), U3.5 (GND), U3.21 (GND), U4.1 (GND/ADJ)
unnamed: C1.1, U3.8 (PB7), Y1.2
unnamed: C2.1, D1.2, U2.1 (INPUT)
unnamed: C3.1, U3.7 (PB6), U3.15 (PB3), Y1.1
unnamed: C4.1, C5.1, U2.3 (OUTPUT), U4.3 (VIN)
unnamed: C6.1, U3.20 (AREF)
unnamed: D1.1, J1.1
unnamed: D2.1 (+), R5.2 (B)
unnamed: D3.1 (+), R6.2 (B)
unnamed: D4.1 (+), R7.2 (B)
unnamed: D5.1, Q1.1 (C)
unnamed: J2.2, R1.1 (A), U3.23 (PC0)
unnamed: R4.1 (A), U3.28 (PC5)
unnamed: R3.1 (A), U3.27 (PC4)
unnamed: J4.1, U3.16 (PB4)
unnamed: R2.2 (B), U1.2, U3.29 (PC6/~RESET)
unnamed: Q1.2 (B), R8.2 (B)
unnamed: R5.1 (A), U3.2 (PD4)
unnamed: R6.1 (A), U3.9 (PD5)
unnamed: R7.1 (A), U3.10 (PD6)
unnamed: R8.1 (A), U3.11 (PD7)
VCC: C7.1, C9.1, C10.1, D5.2, R2.1 (A), U3.4 (VCC), U3.6 (VCC), U3.18 (AVCC)
